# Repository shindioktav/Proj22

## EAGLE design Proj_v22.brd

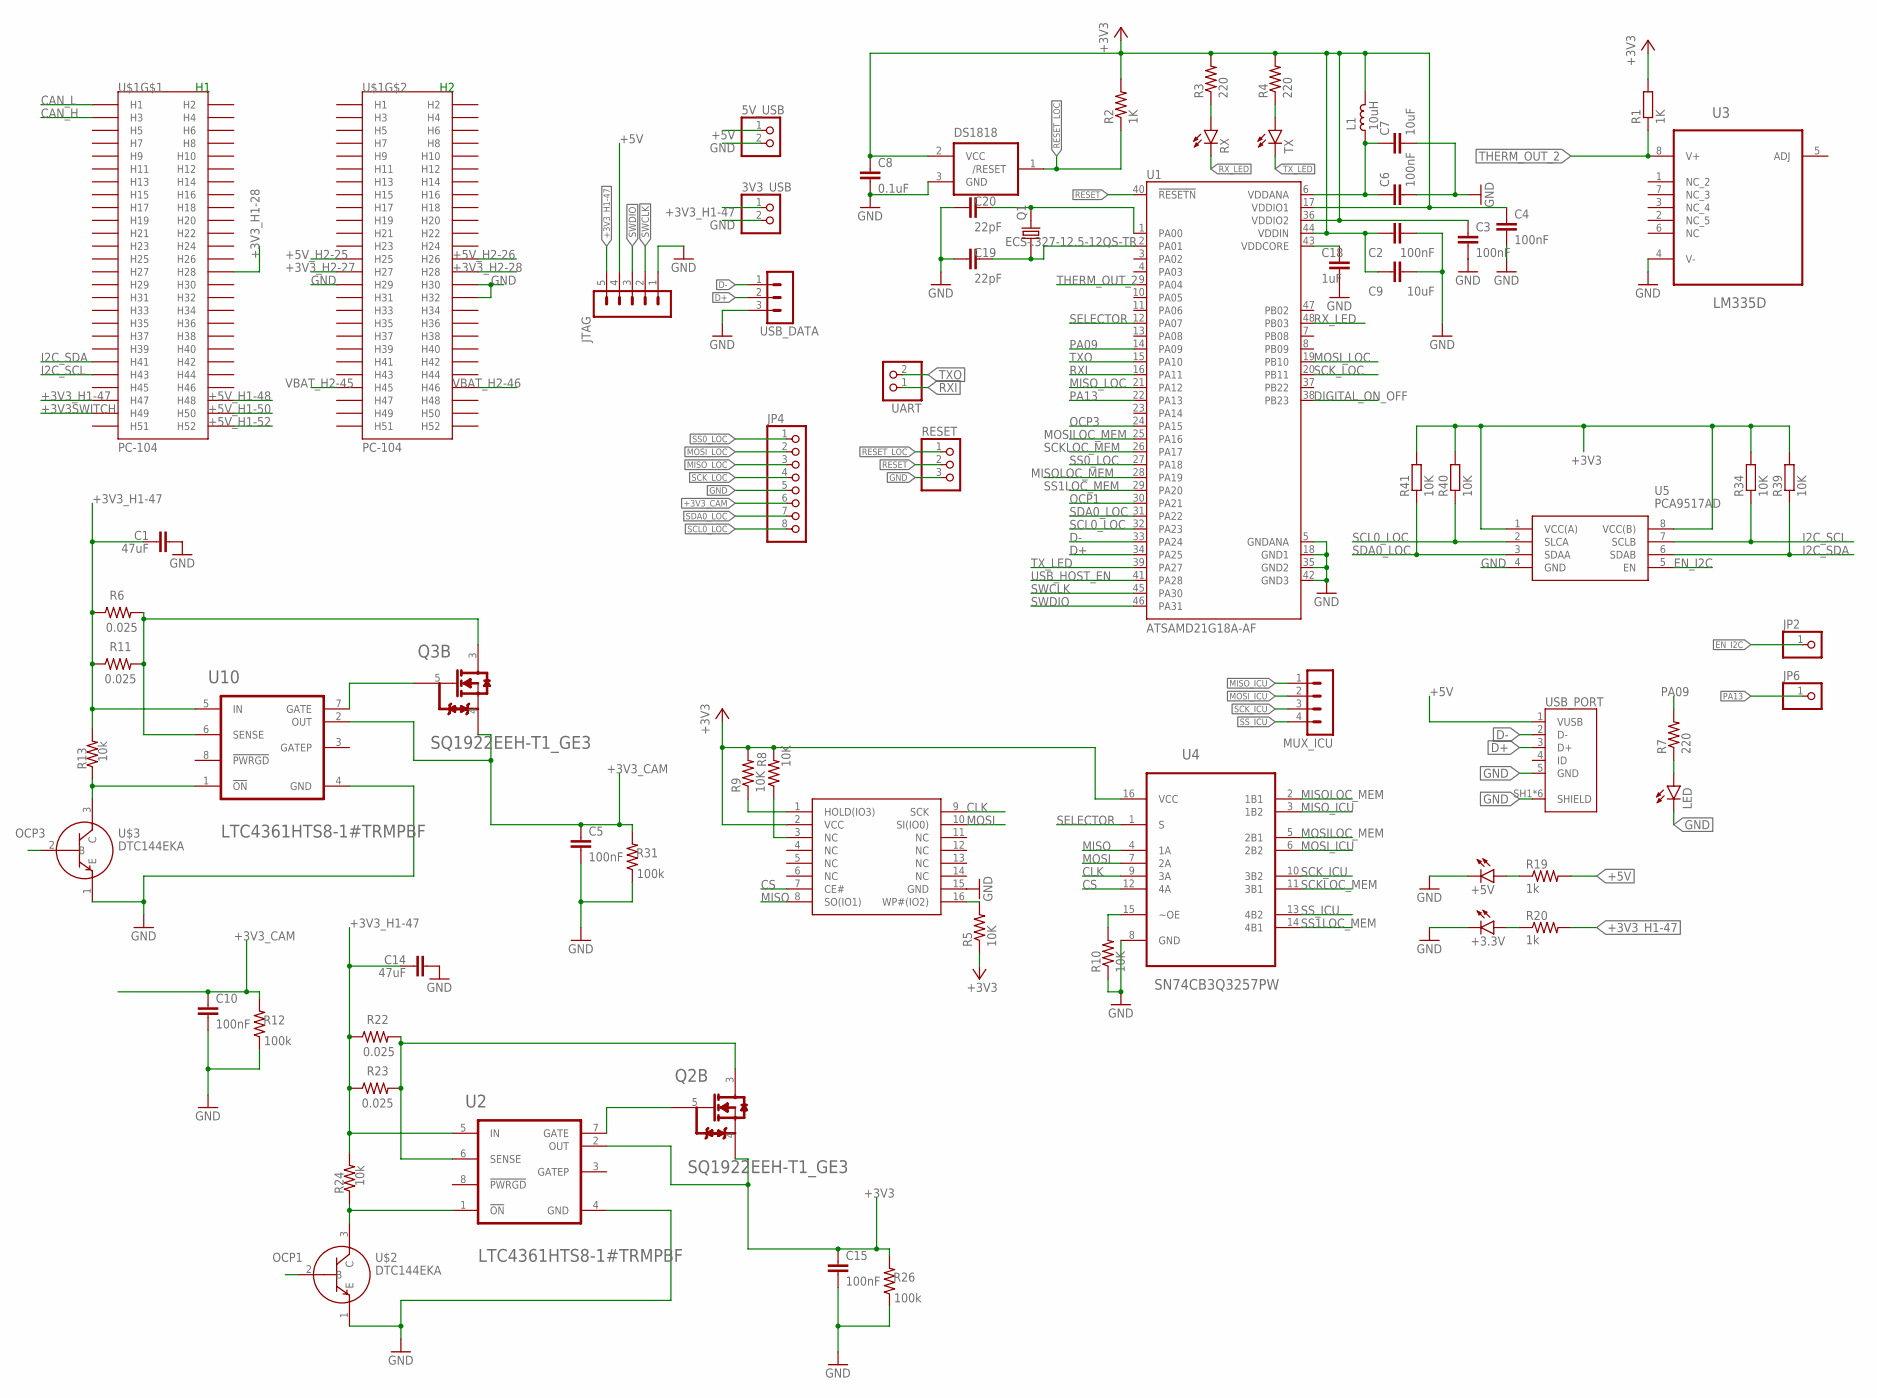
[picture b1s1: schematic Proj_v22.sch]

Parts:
3V3_USB, 5V_USB: PINHD-1X2; 1X02
+3.3V, +5V: LEDCHIP-LED0805; CHIP-LED0805
C1, C14: 47uF; C0805
C2, C3, C4, C6: 100nF; C0805K
C5, C10, C15: 100nF; C0805
C7, C9: 10uF; C0805K
C8: 0.1uF; C0805K
C18: 1uF; C0805K
C19, C20: 22pF; C0805K
JP2, JP6: PINHD-1X1; 1X01
JP4: PINHD-1X8; 1X08
JTAG: MA05-1
L1: 10uH; L0805
LED: LEDCHIP-LED0805; CHIP-LED0805
LOC_MEM: SOIC127P600X175-16NSOIC-16YAS; SOIC127P1032X265-17T480X861N
MUX_ICU: MA04-1
Q1: ECS-.327-12.5-12QS-TR; XTAL_ECS-.327-12.5-12QS-TR
Q2, Q3: VISHAY_SQ1922EEH-T1_GE3VISHAY_SQ1922EEH-T1_GE3_0_0; VISHAY_SQ1922EEH-T1_GE3_0
R1, R2: 1K; M0805
R3, R4, R7: 220; M0805
R5, R8, R9, R10, R34, R39, R40, R41: 10K; M0805
R6, R11, R22, R23: 0.025; R0603
R12, R26, R31: 100k; R0603
R13, R24: 10k; R0603
R19, R20: 1k; M0805
RESET: PINHD-1X3; 1X03
RX: LEDCHIP-LED0805; CHIP-LED0805
TX: LEDCHIP-LED0805; CHIP-LED0805
U1: ATSAMD21G18A-AF; QFP50P900X900X120-48N
U2, U10: LINEAR_TECHNOLOGY_LTC4361HTS8-1#TRMPBFLINEAR_TECH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; LINEAR_TECHNOLOGY_LTC4361HTS8-1#TRMPBF_0
U3: LM335D; SOIC127P600X175-8N
U4: SN74CB3Q3257PW; SOP65P640X120-16N
U5: PCA9517AD; SOIC127P600X175-8N
U$1: PC-104
U$2, U$3: DTC144EKA
U?2: DS1818; SOT23
UART: PINHD-1X2; 1X02
USB_DATA: MA03-1
USB_PORT: 10118192-0001LF; AMPHENOL_10118192-0001LF

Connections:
+3V3: C2.1, C3.1, C4.1, C8.1, C9.1, C15.1, L1.1, LOC_MEM.2 (VCC), Q2.4 (S2), R1.2, R2.2, R3.2, R4.2, R5.1, R8.2, R9.2, R26.2, R34.2, R39.2, R40.2, R41.2, U1.17 (VDDIO1), U1.36 (VDDIO2), U1.44 (VDDIN), U2.2 (OUT), U4.16 (VCC), U5.1 (VCC(A)), U5.8 (VCC(B)), U?2.2 (VCC)
+3V3SWITCH: U$1.P$49 (H49)
+3V3_CAM: C5.1, C10.1, JP4.6, Q3.4 (S2), R12.2, R31.2, U10.2 (OUT)
+3V3_H1-28: U$1.P$28 (H28)
+3V3_H1-47: 3V3_USB.1, C1.1, C14.1, JTAG.5, R6.1, R11.1, R13.2, R20.2, R22.1, R23.1, R24.2, U2.5 (IN), U10.5 (IN), U$1.P$47 (H47)
+3V3_H2-27: U$1.P$79 (H27)
+3V3_H2-28: U$1.P$80 (H28)
+5V: 5V_USB.1, JTAG.4, R19.2, USB_PORT.1 (VUSB)
+5V_H1-48: U$1.P$48 (H48)
+5V_H1-50: U$1.P$50 (H50)
+5V_H1-52: U$1.P$52 (H52)
+5V_H2-25: U$1.P$77 (H25)
+5V_H2-26: U$1.P$78 (H26)
CAN_H: U$1.P$3 (H3)
CAN_L: U$1.P$1 (H1)
CLK: LOC_MEM.9 (SCK), U4.9 (3A)
CS: LOC_MEM.7 (CE#), U4.12 (4A)
D+: U1.34 (PA25), USB_DATA.2, USB_PORT.3 (D+)
D-: U1.33 (PA24), USB_DATA.1, USB_PORT.2 (D-)
DIGITAL_ON_OFF: U1.38 (PB23)
EN_I2C: JP2.1, U5.5 (EN)
GND: 3V3_USB.2, 5V_USB.2, +3.3V.C, +5V.C, C1.2, C2.2, C3.2, C4.2, C5.2, C6.2, C7.2, C8.2, C9.2, C10.2, C14.2, C15.2, C18.2, C19.1, C20.1, JP4.5, JTAG.1, LED.C, LOC_MEM.15 (GND), R10.1, R12.1, R26.1, R31.1, RESET.3, U1.5 (GNDANA), U1.18 (GND1), U1.35 (GND2), U1.42 (GND3), U2.4 (GND), U3.4 (V-), U4.8 (GND), U5.4 (GND), U10.4 (GND), U$1.P$81 (H29), U$1.P$82 (H30), U$1.P$84 (H32), U$2.1 (E), U$3.1 (E), U?2.3 (GND), USB_DATA.3, USB_PORT.5 (GND), USB_PORT.SH1 (SHIELD), USB_PORT.SH2 (SHIELD), USB_PORT.SH3 (SHIELD), USB_PORT.SH4 (SHIELD), USB_PORT.SH5 (SHIELD), USB_PORT.SH6 (SHIELD)
I2C_SCL: R34.1, U5.7 (SCLB), U$1.P$43 (H43)
I2C_SDA: R39.1, U5.6 (SDAB), U$1.P$41 (H41)
ICU_OCP_SESNSE1: Q2.3 (D2), R22.2, R23.2, U2.6 (SENSE)
ICU_OCP_SESNSE3: Q3.3 (D2), R6.2, R11.2, U10.6 (SENSE)
MISO: LOC_MEM.8 (SO(IO1)), U4.4 (1A)
MISOLOC_MEM: U1.28 (PA19), U4.2 (1B1)
MISO_ICU: MUX_ICU.1, U4.3 (1B2)
MISO_LOC: JP4.3, U1.21 (PA12)
MOSI: LOC_MEM.10 (SI(IO0)), U4.7 (2A)
MOSILOC_MEM: U1.25 (PA16), U4.5 (2B1)
MOSI_ICU: MUX_ICU.2, U4.6 (2B2)
MOSI_LOC: JP4.2, U1.19 (PB10)
unnamed: C20.2, Q1.2, U1.1 (PA00)
unnamed: LOC_MEM.16 (WP#(IO2)), R5.2
unnamed: LOC_MEM.1 (HOLD(IO3)), R9.1
unnamed: LOC_MEM.3 (NC), R8.1
unnamed: C6.1, C7.1, L1.2, U1.6 (VDDANA)
unnamed: +5V.A, R19.1
unnamed: R24.1, U2.1 (!ON!), U$2.3 (C)
unnamed: +3.3V.A, R20.1
unnamed: R3.1, RX.A
unnamed: C18.1, U1.43 (VDDCORE)
unnamed: C19.2, Q1.1, U1.2 (PA01)
unnamed: R4.1, TX.A
unnamed: R13.1, U10.1 (!ON!), U$3.3 (C)
unnamed: LED.A, R7.1
unnamed: Q3.5 (G2), U10.7 (GATE)
unnamed: Q2.5 (G2), U2.7 (GATE)
unnamed: R10.2, U4.15 (~OE)
OCP1: U1.30 (PA21), U$2.2 (B)
OCP3: U1.24 (PA15), U$3.2 (B)
PA09: R7.2, U1.14 (PA09)
PA13: JP6.1, U1.22 (PA13)
RESET: RESET.2, U1.40 (!RESETN)
RESET_LOC: R2.1, RESET.1, U?2.1 (/RESET)
RXI: U1.16 (PA11), UART.1
RX_LED: RX.C, U1.48 (PB03)
SCKLOC_MEM: U1.26 (PA17), U4.11 (3B1)
SCK_ICU: MUX_ICU.3, U4.10 (3B2)
SCK_LOC: JP4.4, U1.20 (PB11)
SCL0_LOC: JP4.8, R40.1, U1.32 (PA23), U5.2 (SLCA)
SDA0_LOC: JP4.7, R41.1, U1.31 (PA22), U5.3 (SDAA)
SELECTOR: U1.12 (PA07), U4.1 (S)
SS0_LOC: JP4.1, U1.27 (PA18)
SS1LOC_MEM: U1.29 (PA20), U4.14 (4B1)
SS_ICU: MUX_ICU.4, U4.13 (4B2)
SWCLK: JTAG.2, U1.45 (PA30)
SWDIO: JTAG.3, U1.46 (PA31)
THERM_OUT_2: R1.1, U1.9 (PA04), U3.8 (V+)
TXO: U1.15 (PA10), UART.2
TX_LED: TX.C, U1.39 (PA27)
USB_HOST_EN: U1.41 (PA28)
VBAT_H2-45: U$1.P$97 (H45)
VBAT_H2-46: U$1.P$98 (H46)

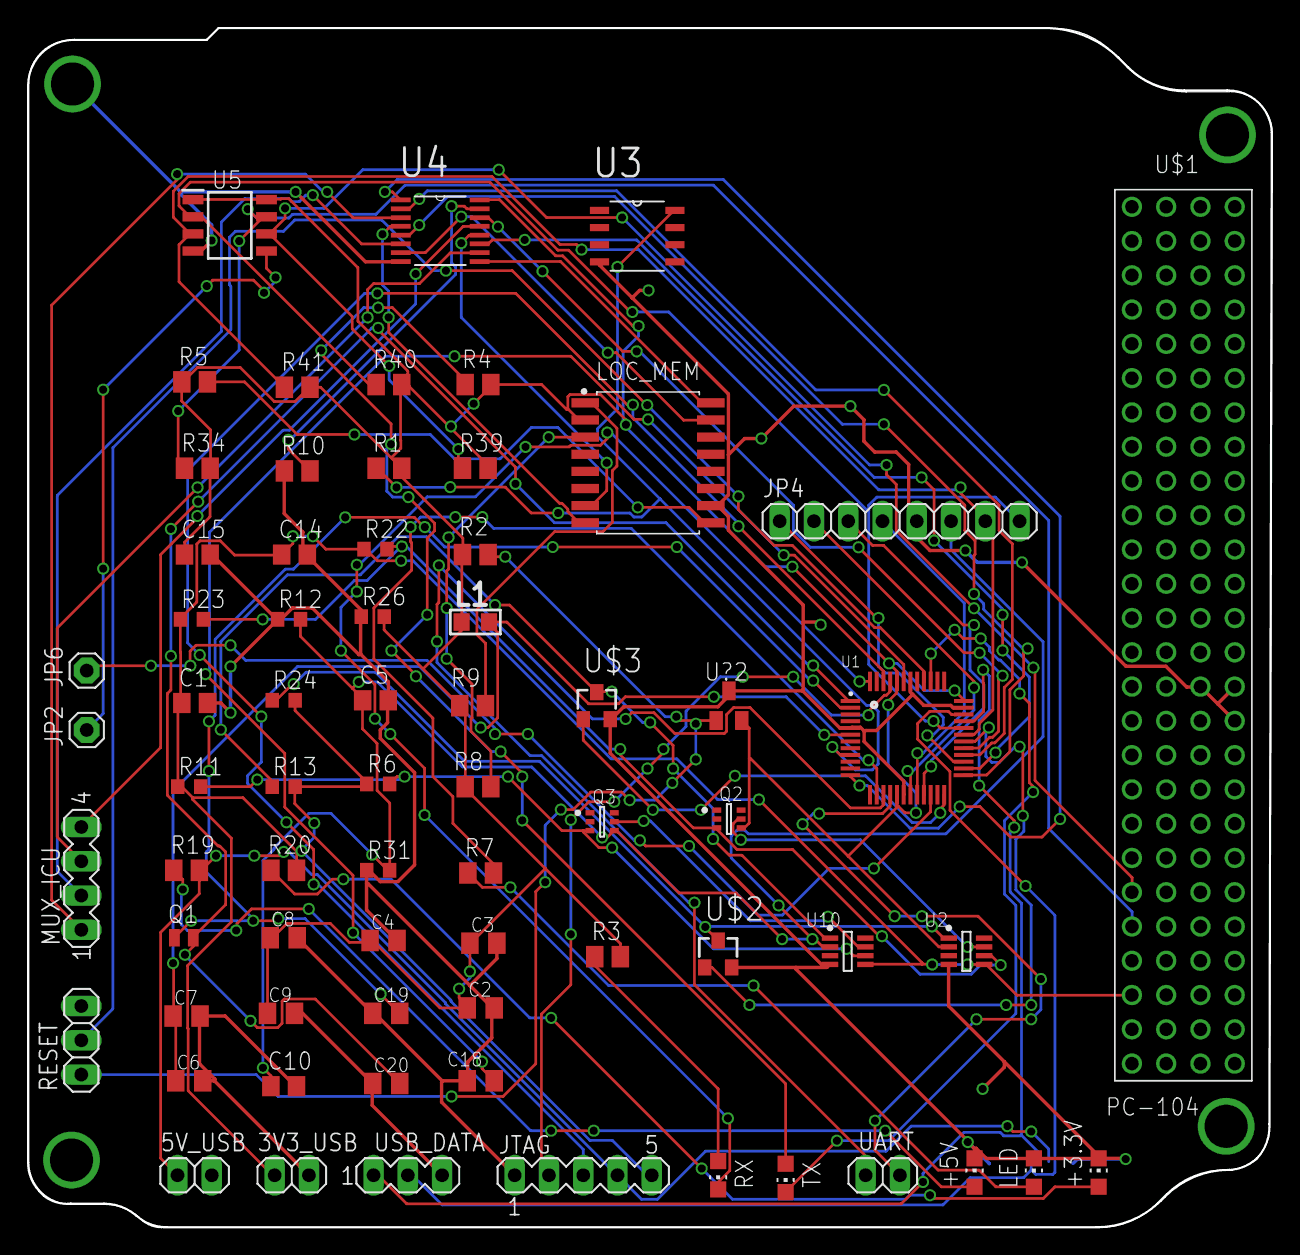
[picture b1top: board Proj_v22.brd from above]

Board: 2 copper layers, 92.2 x 88.9 mm, 70 parts (1 on the bottom side), 61 nets.

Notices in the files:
parts and their libraries:
rc-master-smd: Copyright (C) 2007, Bob Starr
